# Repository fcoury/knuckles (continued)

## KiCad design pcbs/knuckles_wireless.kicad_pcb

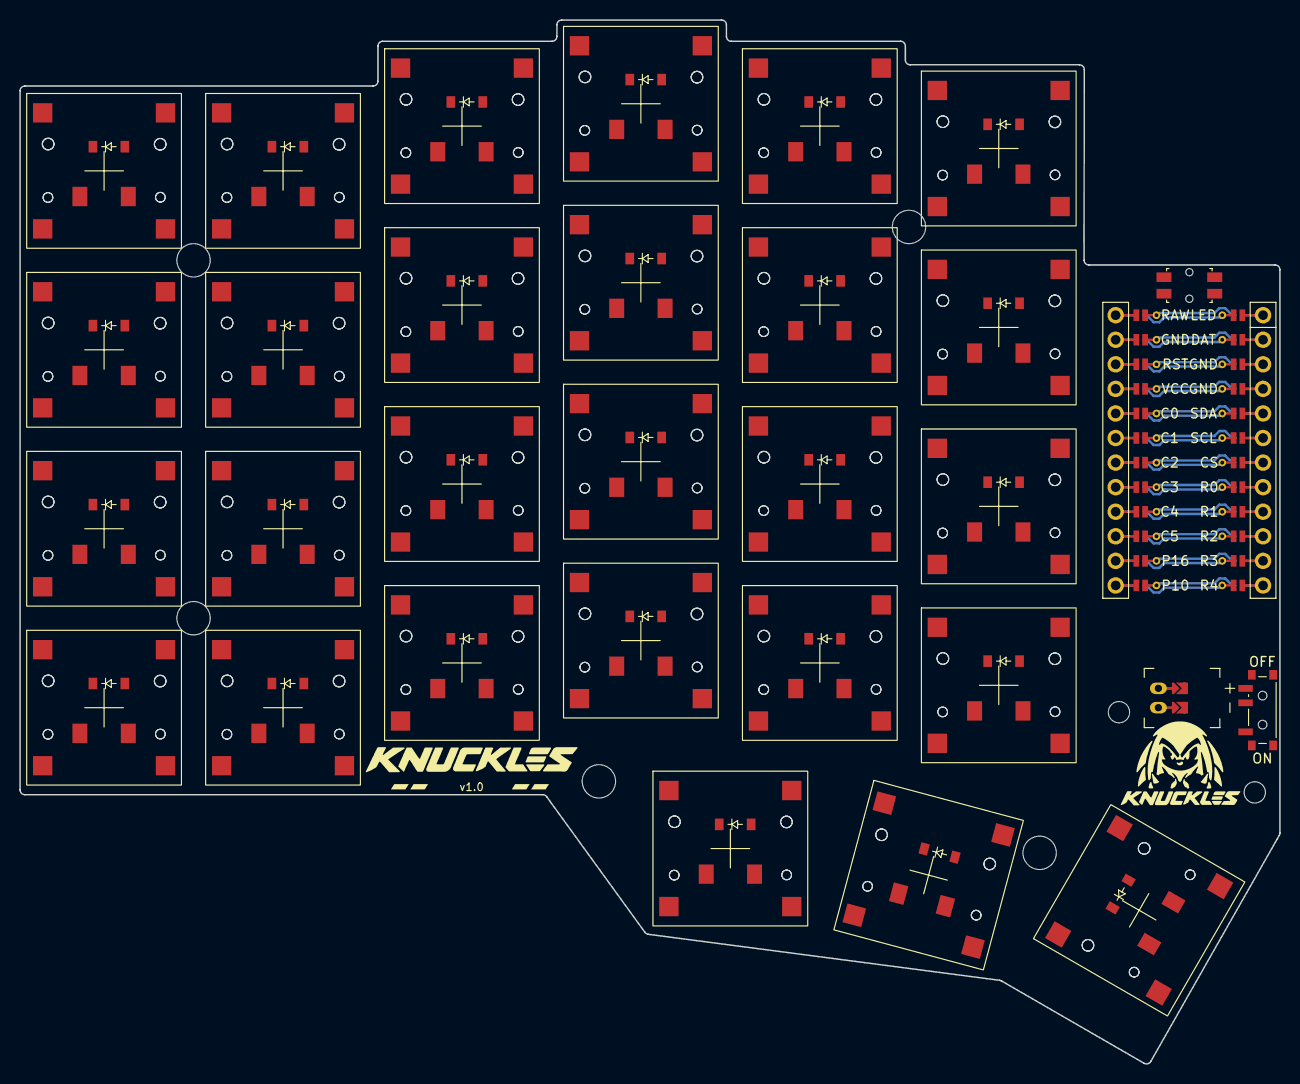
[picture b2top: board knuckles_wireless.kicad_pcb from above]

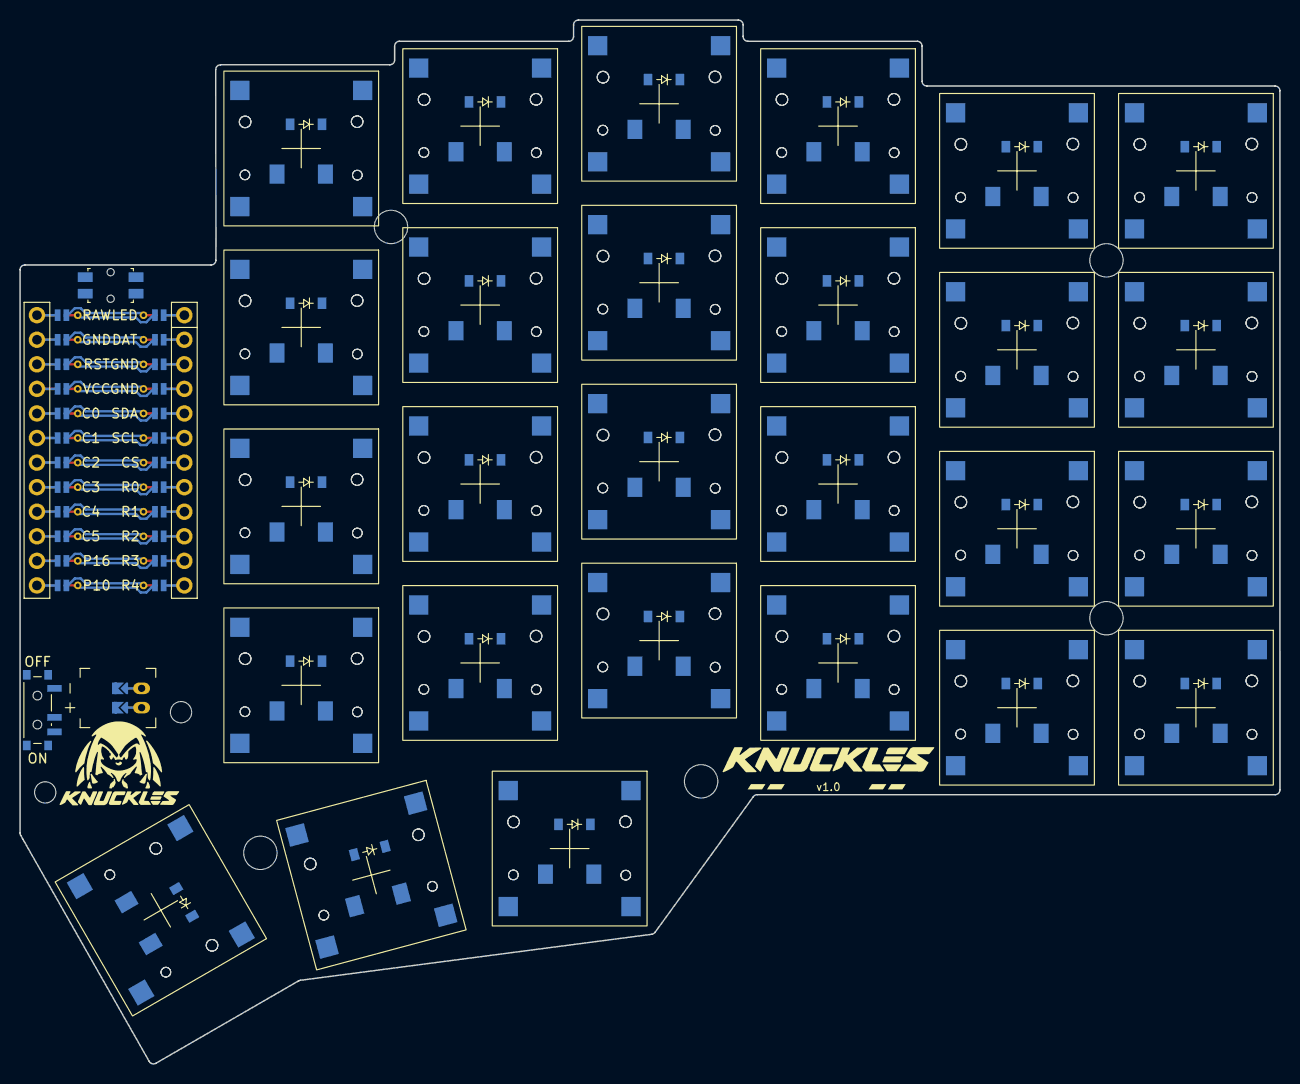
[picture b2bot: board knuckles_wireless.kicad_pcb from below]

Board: 2 copper layers, 130.3 x 107.9 mm, 121 parts (54 on the bottom side), 71 nets.

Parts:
ART1: knuckles_artwork_badge
ART2: knuckles_artwork_wordmark
D1, D2, D3, D4, D5, D6, D7, D8, D9, D10, D11, D12, D13, D14, D15, D16, D17, D18, D19, D20, D21, D22, D23, D24, D25, D26, D27, D28, D29, D30, D31, D32, D33, D34, D35, D36, D37, D38, D39, D40, D41, D42, D43, D44, D45, D46, D47, D48, D49, D50, D51, D52, D53, D54: diode_tht_sod123
JST1: battery_connector_jst_ph_2
MCU1: mcu_nice_nano
MH1, MH2, MH3, MH4, MH5, MH6, MH7: mounting_hole_npth
PWR1: power_switch_smd_side
RST1: reset_switch_smd_side
S1, S2, S3, S4, S5, S6, S7, S8, S9, S10, S11, S12, S13, S14, S15, S16, S17, S18, S19, S20, S21, S22, S23, S24, S25, S26, S27, S28, S29, S30, S31, S32, S33, S34, S35, S36, S37, S38, S39, S40, S41, S42, S43, S44, S45, S46, S47, S48, S49, S50, S51, S52, S53, S54: CPG1316S01D02

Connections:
BAT_P: JST1.1, PWR1.1, PWR1.3
C0: MCU1.120, S1.1, S2.1, S3.1, S4.1, S28.1, S29.1, S30.1, S31.1
C1: MCU1.119, S5.1, S6.1, S7.1, S8.1, S32.1, S33.1, S34.1, S35.1
C2: MCU1.118, S9.1, S10.1, S11.1, S12.1, S36.1, S37.1, S38.1, S39.1
C3: MCU1.117, S13.1, S14.1, S15.1, S16.1, S25.1, S40.1, S41.1, S42.1, S43.1, S52.1
C4: MCU1.116, S17.1, S18.1, S19.1, S20.1, S26.1, S44.1, S45.1, S46.1, S47.1, S53.1
C5: MCU1.115, S21.1, S22.1, S23.1, S24.1, S27.1, S48.1, S49.1, S50.1, S51.1, S54.1
GND: JST1.2, MCU1.103, MCU1.104, MCU1.123, RST1.1, RST1.3
JST1_1: JST1.11, JST1.21, JST1.31
JST1_2: JST1.12, JST1.22, JST1.32
R0: D4.1, D8.1, D12.1, D16.1, D20.1, D24.1, D31.1, D35.1, D39.1, D43.1, D47.1, D51.1, MCU1.108
R1: D3.1, D7.1, D11.1, D15.1, D19.1, D23.1, D30.1, D34.1, D38.1, D42.1, D46.1, D50.1, MCU1.109
R2: D2.1, D6.1, D10.1, D14.1, D18.1, D22.1, D29.1, D33.1, D37.1, D41.1, D45.1, D49.1, MCU1.110
R3: D1.1, D5.1, D9.1, D13.1, D17.1, D21.1, D28.1, D32.1, D36.1, D40.1, D44.1, D48.1, MCU1.111
R4: D25.1, D26.1, D27.1, D52.1, D53.1, D54.1, MCU1.112
RAW: MCU1.124, PWR1.2
RST: MCU1.122, RST1.2, RST1.4
far_home_B: D27.2, S27.2
far_home_F: D54.2, S54.2
index_bottom_B: D17.2, S17.2
index_bottom_F: D44.2, S44.2
index_home_B: D18.2, S18.2
index_home_F: D45.2, S45.2
index_numbers_B: D20.2, S20.2
index_numbers_F: D47.2, S47.2
index_top_B: D19.2, S19.2
index_top_F: D46.2, S46.2
inner_bottom_B: D21.2, S21.2
inner_bottom_F: D48.2, S48.2
inner_home_B: D22.2, S22.2
inner_home_F: D49.2, S49.2
inner_numbers_B: D24.2, S24.2
inner_numbers_F: D51.2, S51.2
inner_top_B: D23.2, S23.2
inner_top_F: D50.2, S50.2
mid_home_B: D26.2, S26.2
mid_home_F: D53.2, S53.2
middle_bottom_B: D13.2, S13.2
middle_bottom_F: D40.2, S40.2
middle_home_B: D14.2, S14.2
middle_home_F: D41.2, S41.2
middle_numbers_B: D16.2, S16.2
middle_numbers_F: D43.2, S43.2
middle_top_B: D15.2, S15.2
middle_top_F: D42.2, S42.2
near_home_B: D25.2, S25.2
near_home_F: D52.2, S52.2
outer_bottom_B: D1.2, S1.2
outer_bottom_F: D28.2, S28.2
outer_home_B: D2.2, S2.2
outer_home_F: D29.2, S29.2
outer_numbers_B: D4.2, S4.2
outer_numbers_F: D31.2, S31.2
outer_top_B: D3.2, S3.2
outer_top_F: D30.2, S30.2
pinky_bottom_B: D5.2, S5.2
pinky_bottom_F: D32.2, S32.2
pinky_home_B: D6.2, S6.2
pinky_home_F: D33.2, S33.2
pinky_numbers_B: D8.2, S8.2
pinky_numbers_F: D35.2, S35.2
pinky_top_B: D7.2, S7.2
pinky_top_F: D34.2, S34.2
ring_bottom_B: D9.2, S9.2
ring_bottom_F: D36.2, S36.2
ring_home_B: D10.2, S10.2
ring_home_F: D37.2, S37.2
ring_numbers_B: D12.2, S12.2
ring_numbers_F: D39.2, S39.2
ring_top_B: D11.2, S11.2
ring_top_F: D38.2, S38.2

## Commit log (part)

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2025-03-01 chore: initial commit
2025-03-02 feat: reversible pg1316s switch footprint
2025-03-02 fix: pg1316s pads cannot be tht on reversible pcb
2025-03-02 feat: board text
2025-03-02 fix: correct board name
2025-03-02 chore: removed old corney_island files
2025-03-02 feat: CI artifact name
2025-03-02 feat: build script and its artifacts
2025-03-17 feat: renamed zeph
2025-03-17 fix: github action board name
2025-03-17 chore: more renaming
2025-03-17 feat: renamed zeph board to knuckles (#1)
    * feat: renamed zeph
    * fix: github action board name
    * chore: more renaming
2025-09-05 docs: README
2025-09-05 chore: README.md
2025-09-05 chore: LICENSE
